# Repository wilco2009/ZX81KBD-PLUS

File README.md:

# ZX81KBD-PLUS
 Joystick, PS2 & USB keyboard interface for the ZX81

 ## INTERFACE COMPONENTS

 COMPONENT LIST
 |  Component |  Quantity |
 | ------| --------| 
 | Arduino nano R3	1
 | Push Button 6x6 | 2
 | DB9 male	| 1
 | Mini DIN	9 PIN | 1
 | PCF8574P	| 1
 | USB Host Shield	| 1
 | OLED 128x32 I2C	| 1
 | XC9572XL-PLCC44	| 1
 | LM1117 3v3 regulator SOT223| 1
 | Res 100K	| 2
 | Res 4K7	| 8
 | DIP16 socket	| 1
 | PLCC44 socket (Though hole)	| 1
 | pin header male 1x40 | 1
 | pin header male 1x40 (long pins)	| 1
 | pin header female 1x40	| 2
 | 74AHC125D SOP14	| 1
 | EDGE CONNECTOR | 1
 
Once the interface is assembled, the first thing we have to do is program the arduino (using the arduino IDE) or the avrdude.
We must also program the CPLD using the Xilinx IMPACT program and connecting a programming cable to the JTAG connector.

## REPLACING THE USB HOST SHIELD CHIP
Unless we buy an original USB Host Shield from the official Arduino store, it is very likely that we will end up with a defective board from Aliexpress. The Chinese manufacturers have not strictly followed the original scheme and have used a 74HC125D instead of a 74AHC125D indicated in the original scheme.

The good news is that by replacing this chip it is very likely that we will have a fully functional board, the bad news is that we will have to desolder the old chip and solder the new one.
In the photo you can see the chip that needs to be replaced.

## MAIN SCREEN

The main screen of the OLED display is divided into two sections.
On the left we have a representation of the zx81 keyboard, and on the right a representation of the joystick with its three buttons (A B and FIRE)
When you press any key on the keyboard or any button on the joystick we will see the pressure on the display.
Additionally, in the joystick section we can see which keys are configured for each of the joystick buttons.

## INTERFACE CONFIGURATION

To enter the configuration menu we can do it in two ways:
- Pressing the configuration button
- Pressing F10 on the keyboard

Once inside the menu we can move through the options using the joystick or the keyboard cursor arrows. 
To select an option we will press the fire button on the joystick or the enter key on the keyboard.

### SELECTION OF KEYBOARD LAYOUT

The first option that appears when we access the menu is the one that will allow us to choose the keyboard layout.

The system is prepared for the following distributions:
- "US" - USA
- "UK" - United Kingdom
- "ES" - Spain
- "DE" - Germany

The active keyboard will be marked with an asterisk.
We can change the active keyboard with the up/down arrows on the keyboard or joystick and select with enter or the fire button.
The ESC key will return to the main menu.

### REDEFINING JOYSTICK KEYS

To redefine the joystick keys we will select the second option from the main menu by moving down with the arrow and press enter/fire.
After this, a screen identical to the main screen will appear but with the first joystick button to be redefined (UP) flashing.
We will select the key we want with the arrows in the left section of the screen and press ENTER or fire.
We can also directly press the key that we want to assign, except in the case of the cursor and enter keys, which would have to be selected by the first method mentioned.
By pressing the ESC or A key on the joystick we will go to the next button without modifying the current one.

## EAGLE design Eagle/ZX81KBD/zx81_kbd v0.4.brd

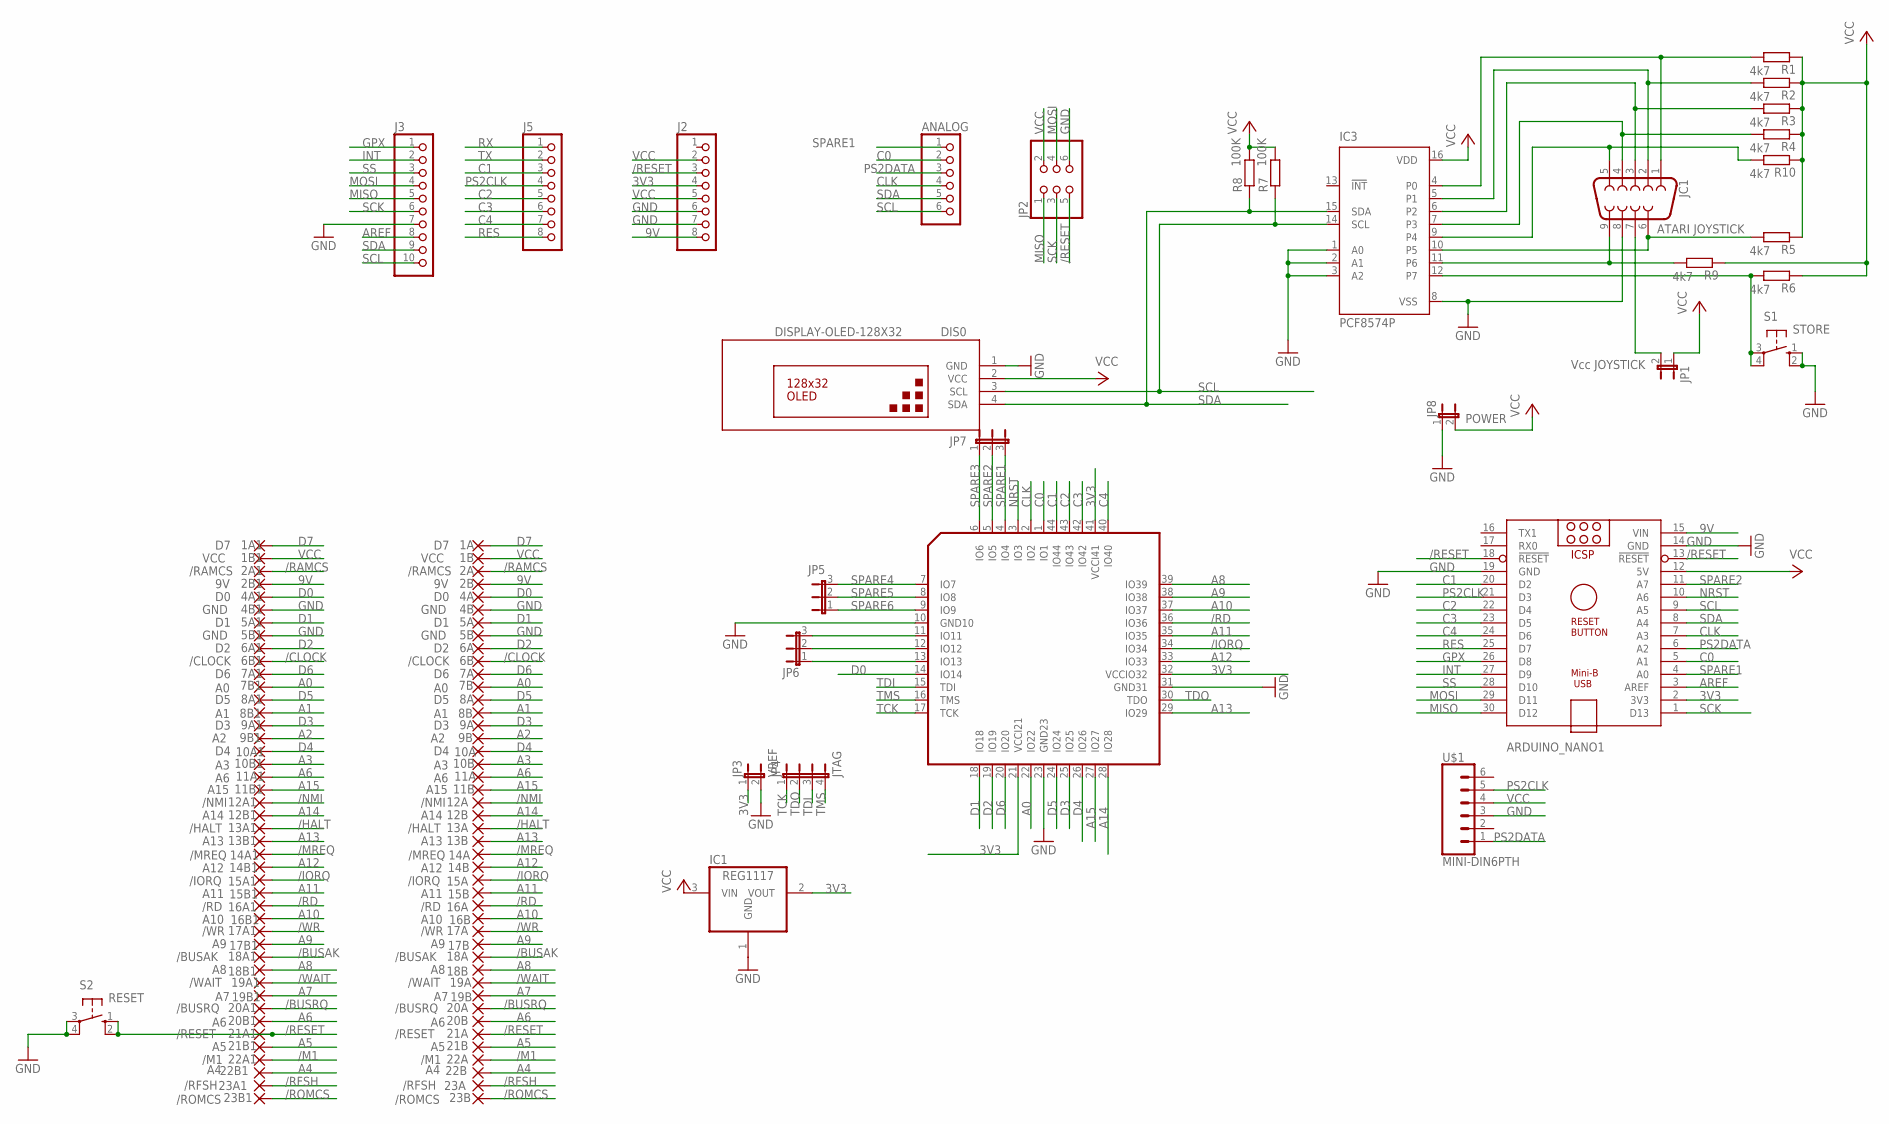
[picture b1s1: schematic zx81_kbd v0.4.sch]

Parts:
1A, 1A1: D7; EDGEPIN
1B, 1B1: VCC; EDGEPIN
2A, 2A1: /RAMCS; EDGEPIN
2B, 2B1: 9V; EDGEPIN
4A, 4A1: D0; EDGEPIN
4B, 4B1, 5B, 5B1: GND; EDGEPIN
5A, 5A1: D1; EDGEPIN
6A, 6A1: D2; EDGEPIN
6B, 6B1: /CLOCK; EDGEPIN
7A, 7A1: D6; EDGEPIN
7B, 7B1: A0; EDGEPIN
8A, 8A1: D5; EDGEPIN
8B, 8B1: A1; EDGEPIN
9A, 9A1: D3; EDGEPIN
9B, 9B1: A2; EDGEPIN
10A, 10A1: D4; EDGEPIN
10B, 10B1: A3; EDGEPIN
11A, 11A1, 20B, 20B1: A6; EDGEPIN
11B, 11B1: A15; EDGEPIN
12A, 12A1: /NMI; EDGEPIN
12B, 12B1: A14; EDGEPIN
13A, 13A1: /HALT; EDGEPIN
13B, 13B1: A13; EDGEPIN
14A, 14A1: /MREQ; EDGEPIN
14B, 14B1: A12; EDGEPIN
15A, 15A1: /IORQ; EDGEPIN
15B, 15B1: A11; EDGEPIN
16A, 16A1: /RD; EDGEPIN
16B, 16B1: A10; EDGEPIN
17A, 17A1: /WR; EDGEPIN
17B, 17B1: A9; EDGEPIN
18A, 18A1: /BUSAK; EDGEPIN
18B, 18B1: A8; EDGEPIN
19A, 19A1: /WAIT; EDGEPIN
19B, 19B1: A7; EDGEPIN
20A, 20A1: /BUSRQ; EDGEPIN
21A, 21A1: /RESET; EDGEPIN
21B, 21B1: A5; EDGEPIN
22A, 22A1: /M1; EDGEPIN
22B, 22B1: A4; EDGEPIN
23A, 23A1: /RFSH; EDGEPIN
23B, 23B1: /ROMCS; EDGEPIN
ANALOG: PINHD-1X6; 1X06
ARDUINO_NANO1: ARDUINO_NANO
DIS0: DISPLAY-OLED-128X32
IC1: REG1117; SOT223
IC3: PCF8574P; DIL16
J2, J5: PINHD-1X8; 1X08
J3: PINHD-1X10; 1X10
JC1: ATARI JOYSTICK; DB9_MALE
JP1: Vcc JOYSTICK; JP1
JP2: PINHD-2X3; 2X03
JP3: VREF; JP1
JP4: JTAG; JP4
JP5, JP6, JP7: JP2E; JP2
JP8: POWER; JP1
R1, R2, R3, R4, R5, R6, R9, R10: 4k7; 0204/7
R7, R8: 100K; 0204/7
S1: STORE; B3F-10XX_11MM
S2: RESET; B3F-10XX_11MM
U$1: MINI-DIN6PTH; MINI-DIN6
XC95CPLD: XC9572PLC; 3M44

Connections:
3V3: ARDUINO_NANO1.2 (3V3), IC1.2 (VOUT), J2.4, JP3.1, XC95CPLD.21 (VCCI21), XC95CPLD.32 (VCCIO32), XC95CPLD.41 (VCCI41)
9V: 2B.1, 2B1.1, ARDUINO_NANO1.15 (VIN), J2.8
/BUSAK: 18A.1, 18A1.1
/BUSRQ: 20A.1, 20A1.1
/CLOCK: 6B.1, 6B1.1
/HALT: 13A.1, 13A1.1
/IORQ: 15A.1, 15A1.1, XC95CPLD.34 (IO34)
/M1: 22A.1, 22A1.1
/MREQ: 14A.1, 14A1.1
/NMI: 12A.1, 12A1.1
/RAMCS: 2A.1, 2A1.1
/RD: 16A.1, 16A1.1, XC95CPLD.36 (IO36)
/RESET: 21A.1, 21A1.1, ARDUINO_NANO1.13 (!RESET), ARDUINO_NANO1.18 (!RESET), J2.3, JP2.5, S2.1 (S), S2.2 (S1)
/RFSH: 23A.1, 23A1.1
/ROMCS: 23B.1, 23B1.1
/WAIT: 19A.1, 19A1.1
/WR: 17A.1, 17A1.1
A0: 7B.1, 7B1.1, XC95CPLD.22 (IO22)
A1: 8B.1, 8B1.1
A2: 9B.1, 9B1.1
A3: 10B.1, 10B1.1
A4: 22B.1, 22B1.1
A5: 21B.1, 21B1.1
A6: 11A.1, 11A1.1, 20B.1, 20B1.1
A7: 19B.1, 19B1.1
A8: 18B.1, 18B1.1, XC95CPLD.39 (IO39)
A9: 17B.1, 17B1.1, XC95CPLD.38 (IO38)
A10: 16B.1, 16B1.1, XC95CPLD.37 (IO37)
A11: 15B.1, 15B1.1, XC95CPLD.35 (IO35)
A12: 14B.1, 14B1.1, XC95CPLD.33 (IO33)
A13: 13B.1, 13B1.1, XC95CPLD.29 (IO29)
A14: 12B.1, 12B1.1, XC95CPLD.28 (IO28)
A15: 11B.1, 11B1.1, XC95CPLD.27 (IO27)
AREF: ARDUINO_NANO1.3 (AREF), J3.8
C0: ANALOG.2, ARDUINO_NANO1.5 (A1), XC95CPLD.1 (IO1)
C1: ARDUINO_NANO1.20 (D2), J5.3, XC95CPLD.44 (IO44)
C2: ARDUINO_NANO1.22 (D4), J5.5, XC95CPLD.43 (IO43)
C3: ARDUINO_NANO1.23 (D5), J5.6, XC95CPLD.42 (IO42)
C4: ARDUINO_NANO1.24 (D6), J5.7, XC95CPLD.40 (IO40)
CLK: ANALOG.4, ARDUINO_NANO1.7 (A3), XC95CPLD.2 (IO2)
D0: 4A.1, 4A1.1, XC95CPLD.14 (IO14)
D1: 5A.1, 5A1.1, XC95CPLD.18 (IO18)
D2: 6A.1, 6A1.1, XC95CPLD.19 (IO19)
D3: 9A.1, 9A1.1, XC95CPLD.25 (IO25)
D4: 10A.1, 10A1.1, XC95CPLD.26 (IO26)
D5: 8A.1, 8A1.1, XC95CPLD.24 (IO24)
D6: 7A.1, 7A1.1, XC95CPLD.20 (IO20)
D7: 1A.1, 1A1.1
GND: 4B.1, 4B1.1, 5B.1, 5B1.1, ARDUINO_NANO1.14 (GND), ARDUINO_NANO1.19 (GND), DIS0.1 (GND), IC1.1 (GND), IC3.1 (A0), IC3.2 (A1), IC3.3 (A2), IC3.8 (VSS), J2.6, J2.7, J3.7, JC1.8, JP2.6, JP3.2, JP8.1, S1.1 (S), S1.2 (S1), S2.3, S2.4 (P1), U$1.3, XC95CPLD.10 (GND10), XC95CPLD.23 (GND23), XC95CPLD.31 (GND31)
GPX: ARDUINO_NANO1.26 (D8), J3.1
INT: ARDUINO_NANO1.27 (D9), J3.2
MISO: ARDUINO_NANO1.30 (D12), J3.5, JP2.1
MOSI: ARDUINO_NANO1.29 (D11), J3.4, JP2.4
unnamed: JP6.3, XC95CPLD.11 (IO11)
unnamed: JP6.2, XC95CPLD.12 (IO12)
unnamed: JP6.1, XC95CPLD.13 (IO13)
unnamed: IC3.4 (P0), JC1.1, R1.2
unnamed: IC3.5 (P1), JC1.2, R2.2
unnamed: IC3.6 (P2), JC1.3, R3.2
unnamed: IC3.7 (P3), JC1.4, R4.2
unnamed: IC3.10 (P5), JC1.6, R5.2
unnamed: IC3.9 (P4), JC1.5, R10.2
unnamed: IC3.12 (P7), R6.2, S1.3, S1.4 (P1)
unnamed: JC1.7, JP1.2
unnamed: IC3.11 (P6), JC1.9, R9.2
NRST: ARDUINO_NANO1.10 (A6), XC95CPLD.3 (IO3)
PS2CLK: ARDUINO_NANO1.21 (D3), J5.4, U$1.5
PS2DATA: ANALOG.3, ARDUINO_NANO1.6 (A2), U$1.1
RES: ARDUINO_NANO1.25 (D7), J5.8
RX: J5.1
SCK: ARDUINO_NANO1.1 (D13), J3.6, JP2.3
SCL: ANALOG.6, ARDUINO_NANO1.9 (A5), DIS0.3 (SCL), IC3.14 (SCL), J3.10, R7.1
SDA: ANALOG.5, ARDUINO_NANO1.8 (A4), DIS0.4 (SDA), IC3.15 (SDA), J3.9, R8.1
SPARE1: ANALOG.1, ARDUINO_NANO1.4 (A0), JP7.3, XC95CPLD.4 (IO4)
SPARE2: ARDUINO_NANO1.11 (A7), JP7.2, XC95CPLD.5 (IO5)
SPARE3: JP7.1, XC95CPLD.6 (IO6)
SPARE4: JP5.3, XC95CPLD.7 (IO7)
SPARE5: JP5.2, XC95CPLD.8 (IO8)
SPARE6: JP5.1, XC95CPLD.9 (IO9)
SS: ARDUINO_NANO1.28 (D10), J3.3
TCK: JP4.1, XC95CPLD.17 (TCK)
TDI: JP4.3, XC95CPLD.15 (TDI)
TDO: JP4.2, XC95CPLD.30 (TDO)
TMS: JP4.4, XC95CPLD.16 (TMS)
TX: J5.2
VCC: 1B.1, 1B1.1, ARDUINO_NANO1.12 (5V), DIS0.2 (VCC), IC1.3 (VIN), IC3.16 (VDD), J2.2, J2.5, JP1.1, JP2.2, JP8.2, R1.1, R2.1, R3.1, R4.1, R5.1, R6.1, R7.2, R8.2, R9.1, R10.1, U$1.4

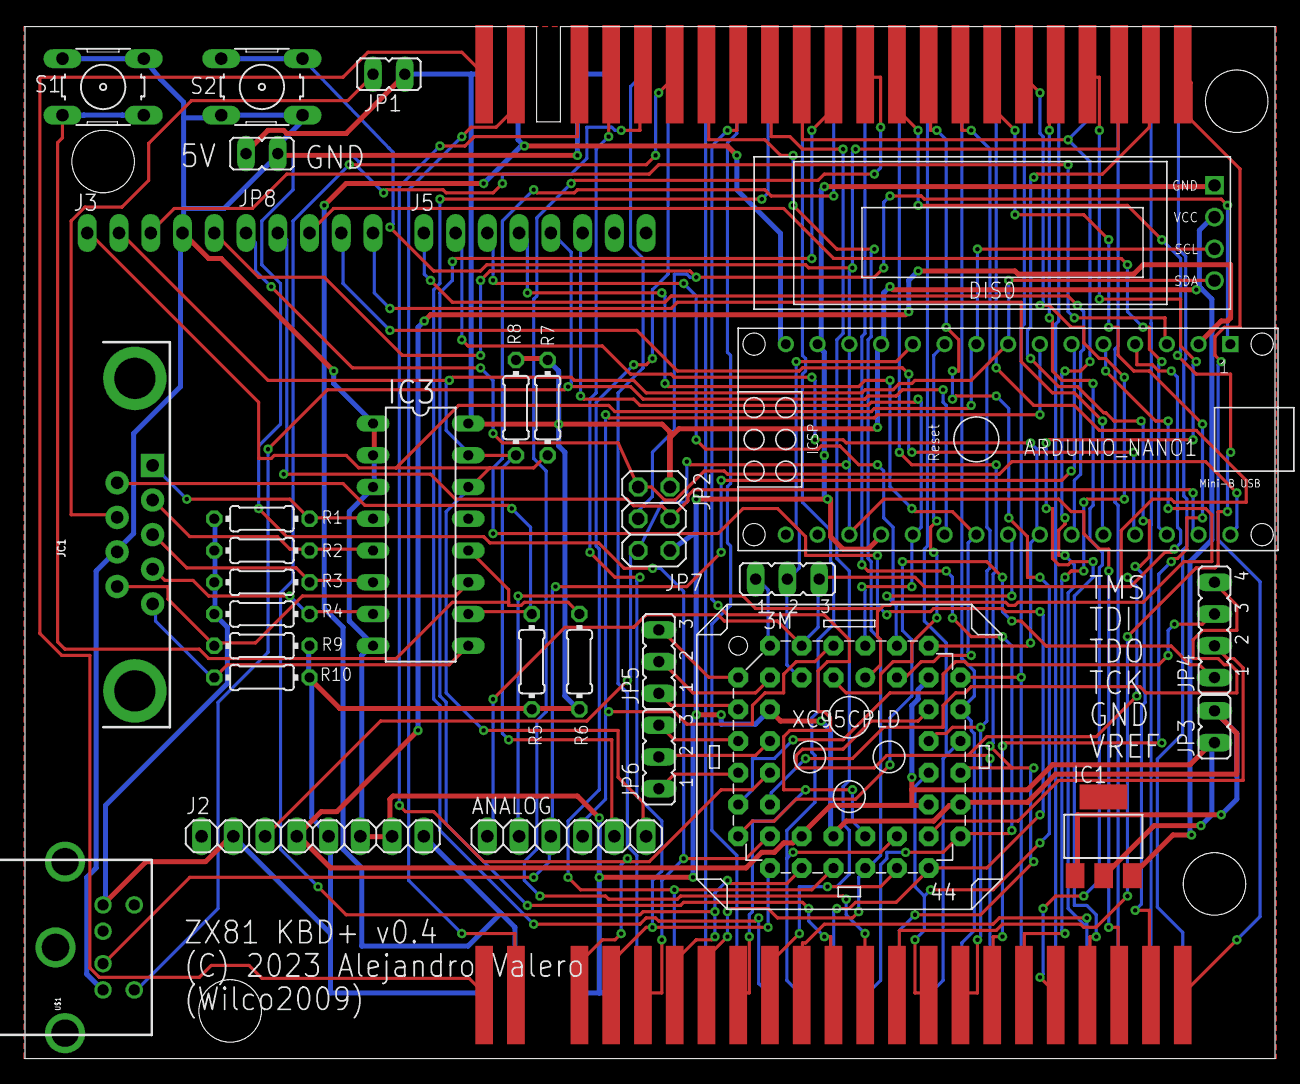
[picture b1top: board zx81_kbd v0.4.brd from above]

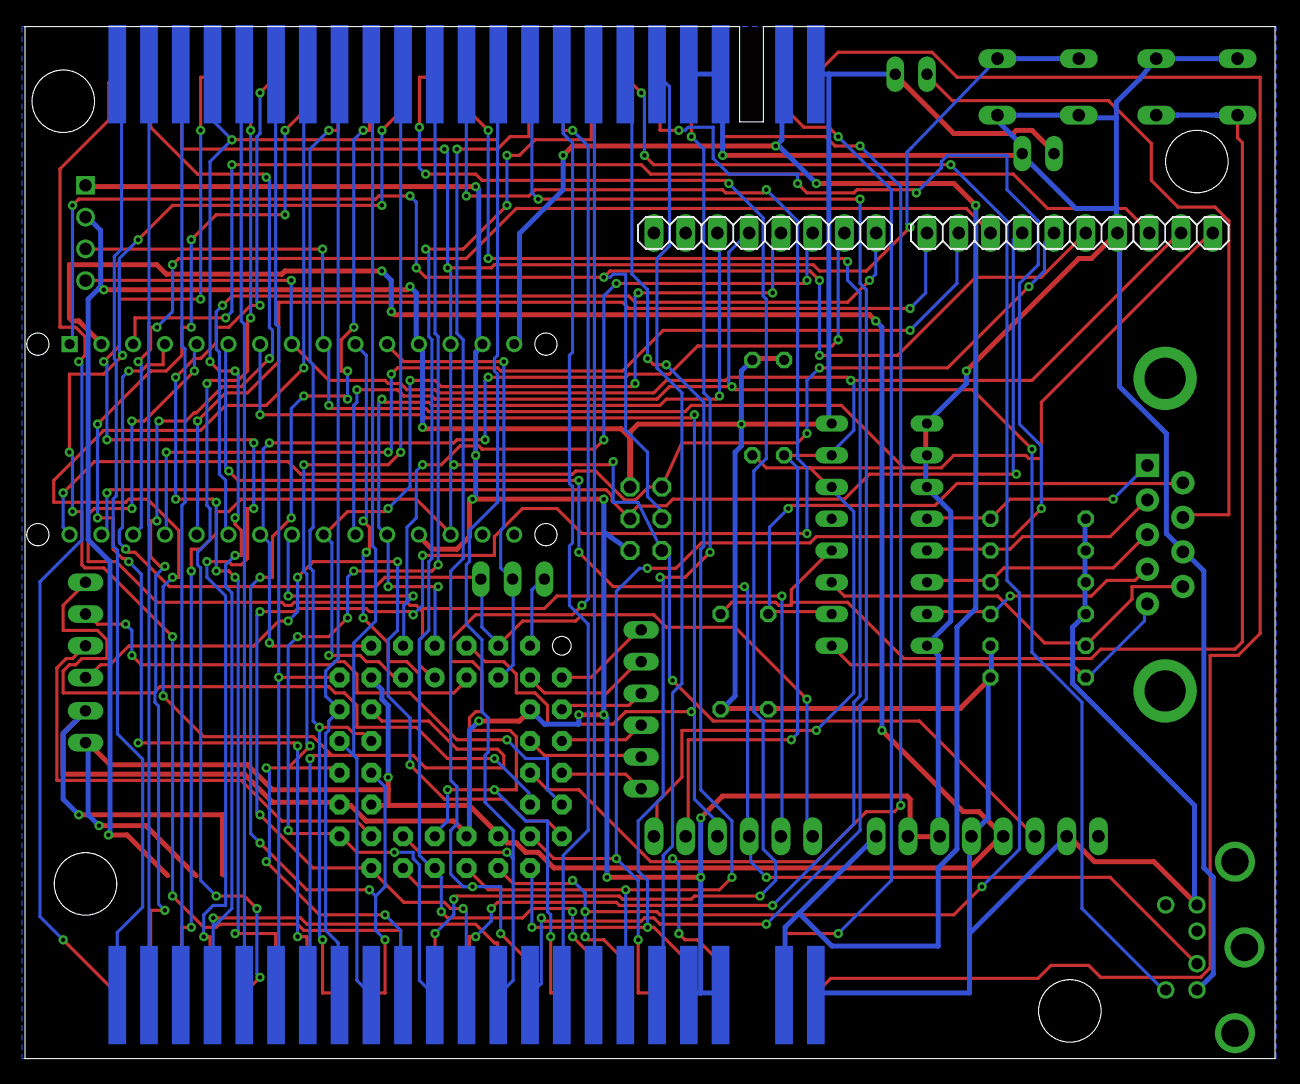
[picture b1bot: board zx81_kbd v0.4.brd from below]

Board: 2 copper layers, 100.0 x 82.5 mm, 119 parts (46 on the bottom side), 84 nets.

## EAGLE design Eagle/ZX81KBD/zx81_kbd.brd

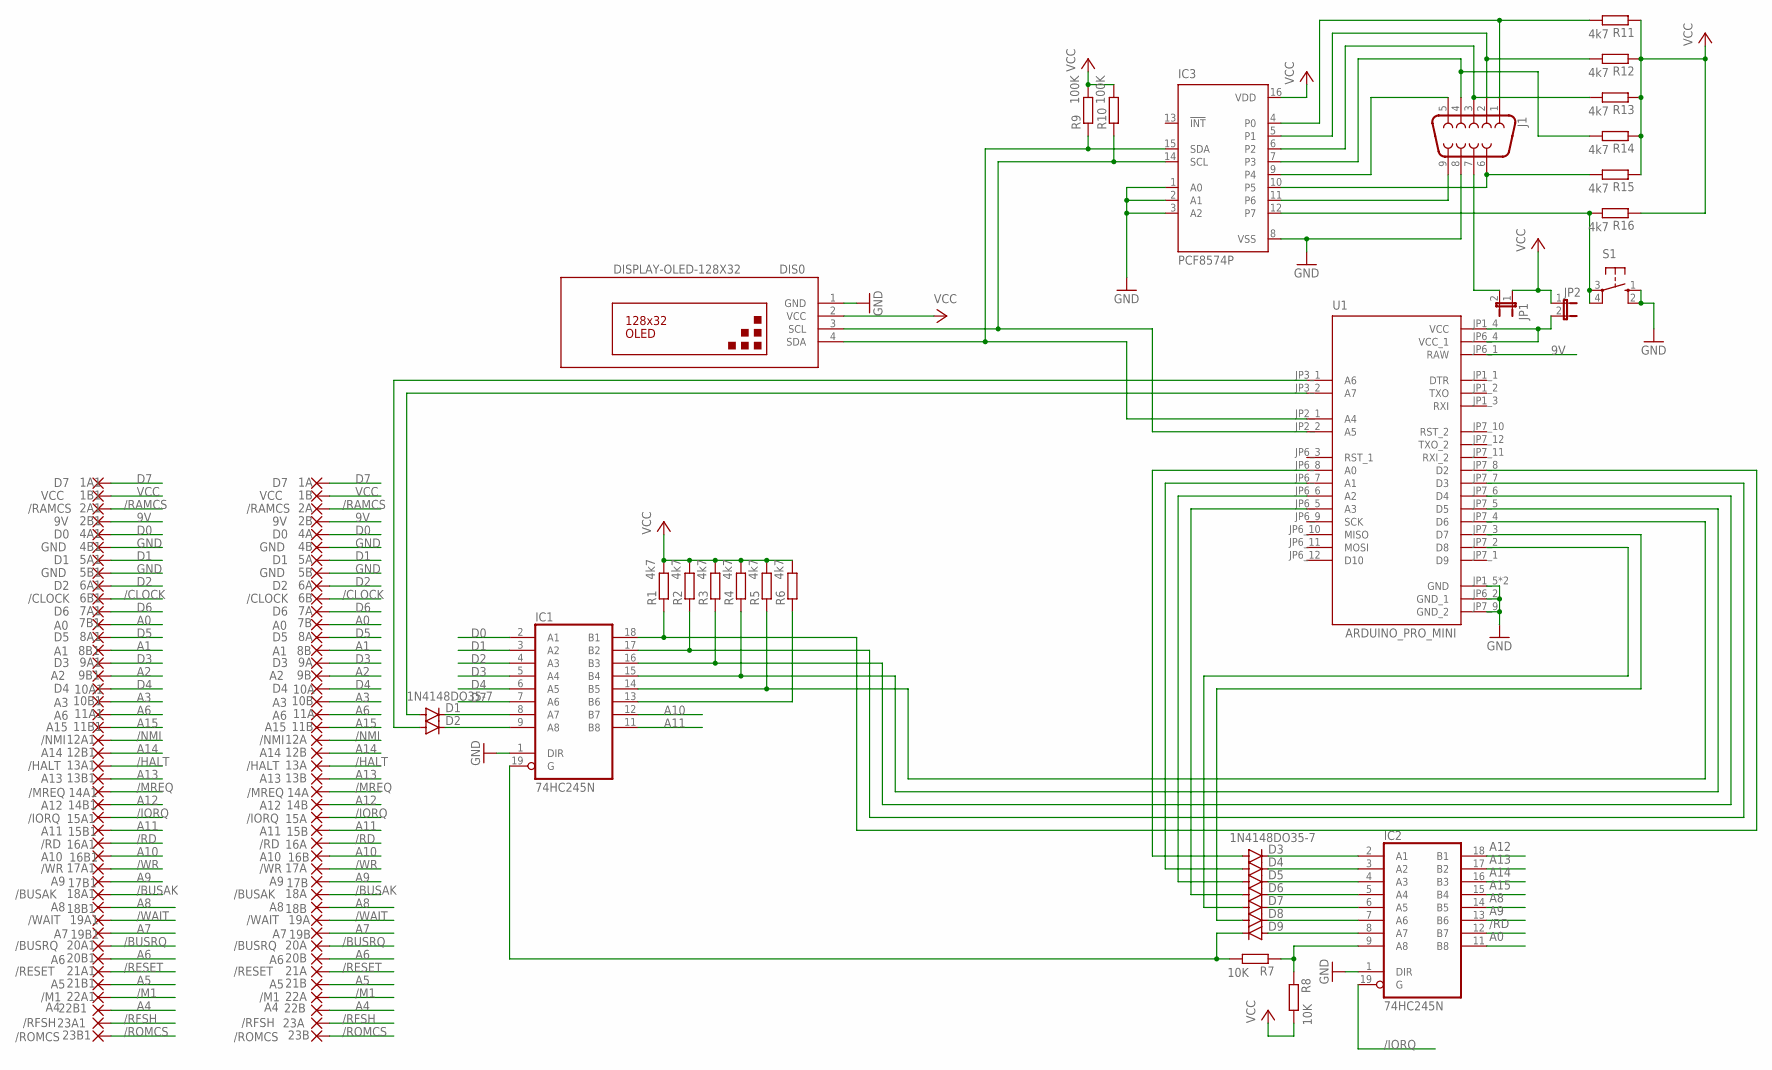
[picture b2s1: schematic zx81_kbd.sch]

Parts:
1A, 1A1: D7; EDGEPIN
1B, 1B1: VCC; EDGEPIN
2A, 2A1: /RAMCS; EDGEPIN
2B, 2B1: 9V; EDGEPIN
4A, 4A1: D0; EDGEPIN
4B, 4B1, 5B, 5B1: GND; EDGEPIN
5A, 5A1: D1; EDGEPIN
6A, 6A1: D2; EDGEPIN
6B, 6B1: /CLOCK; EDGEPIN
7A, 7A1: D6; EDGEPIN
7B, 7B1: A0; EDGEPIN
8A, 8A1: D5; EDGEPIN
8B, 8B1: A1; EDGEPIN
9A, 9A1: D3; EDGEPIN
9B, 9B1: A2; EDGEPIN
10A, 10A1: D4; EDGEPIN
10B, 10B1: A3; EDGEPIN
11A, 11A1, 20B, 20B1: A6; EDGEPIN
11B, 11B1: A15; EDGEPIN
12A, 12A1: /NMI; EDGEPIN
12B, 12B1: A14; EDGEPIN
13A, 13A1: /HALT; EDGEPIN
13B, 13B1: A13; EDGEPIN
14A, 14A1: /MREQ; EDGEPIN
14B, 14B1: A12; EDGEPIN
15A, 15A1: /IORQ; EDGEPIN
15B, 15B1: A11; EDGEPIN
16A, 16A1: /RD; EDGEPIN
16B, 16B1: A10; EDGEPIN
17A, 17A1: /WR; EDGEPIN
17B, 17B1: A9; EDGEPIN
18A, 18A1: /BUSAK; EDGEPIN
18B, 18B1: A8; EDGEPIN
19A, 19A1: /WAIT; EDGEPIN
19B, 19B1: A7; EDGEPIN
20A, 20A1: /BUSRQ; EDGEPIN
21A, 21A1: /RESET; EDGEPIN
21B, 21B1: A5; EDGEPIN
22A, 22A1: /M1; EDGEPIN
22B, 22B1: A4; EDGEPIN
23A, 23A1: /RFSH; EDGEPIN
23B, 23B1: /ROMCS; EDGEPIN
D1, D2, D3, D4, D5, D6, D7, D8, D9: 1N4148DO35-7; DO35-7
DIS0: DISPLAY-OLED-128X32
IC1, IC2: 74HC245N; DIL20
IC3: PCF8574P; DIL16
J1: DB9MALE; DB9_MALE
JP1, JP2: JP1E; JP1
R1, R2, R3, R4, R5, R6, R11, R12, R13, R14, R15, R16: 4k7; 0204/7
R7, R8: 10K; 0204/7
R9, R10: 100K; 0204/7
S1: 10-XX11MM; B3F-10XX_11MM
U1: ARDUINO_PRO_MINI; MODULE_ARDUINO_PRO_MINI

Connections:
9V: 2B.1, 2B1.1, U1.JP6_1 (RAW)
/BUSAK: 18A.1, 18A1.1
/BUSRQ: 20A.1, 20A1.1
/CLOCK: 6B.1, 6B1.1
/HALT: 13A.1, 13A1.1
/IORQ: 15A.1, 15A1.1, IC2.19 (G)
/M1: 22A.1, 22A1.1
/MREQ: 14A.1, 14A1.1
/NMI: 12A.1, 12A1.1
/RAMCS: 2A.1, 2A1.1
/RD: 16A.1, 16A1.1, IC2.12 (B7)
/RESET: 21A.1, 21A1.1
/RFSH: 23A.1, 23A1.1
/ROMCS: 23B.1, 23B1.1
/WAIT: 19A.1, 19A1.1
/WR: 17A.1, 17A1.1
A0: 7B.1, 7B1.1, IC2.11 (B8)
A1: 8B.1, 8B1.1
A2: 9B.1, 9B1.1
A3: 10B.1, 10B1.1
A4: 22B.1, 22B1.1
A5: 21B.1, 21B1.1
A6: 11A.1, 11A1.1, 20B.1, 20B1.1
A7: 19B.1, 19B1.1
A8: 18B.1, 18B1.1, IC2.14 (B5)
A9: 17B.1, 17B1.1, IC2.13 (B6)
A10: 16B.1, 16B1.1, IC1.12 (B7)
A11: 15B.1, 15B1.1, IC1.11 (B8)
A12: 14B.1, 14B1.1, IC2.18 (B1)
A13: 13B.1, 13B1.1, IC2.17 (B2)
A14: 12B.1, 12B1.1, IC2.16 (B3)
A15: 11B.1, 11B1.1, IC2.15 (B4)
D0: 4A.1, 4A1.1, IC1.2 (A1)
D1: 5A.1, 5A1.1, IC1.3 (A2)
D2: 6A.1, 6A1.1, IC1.4 (A3)
D3: 9A.1, 9A1.1, IC1.5 (A4)
D4: 10A.1, 10A1.1, IC1.6 (A5)
D5: 8A.1, 8A1.1
D6: 7A.1, 7A1.1
D7: 1A.1, 1A1.1, IC1.7 (A6)
GND: 4B.1, 4B1.1, 5B.1, 5B1.1, DIS0.1 (GND), IC1.1 (DIR), IC1.10 (GND), IC2.1 (DIR), IC2.10 (GND), IC3.1 (A0), IC3.2 (A1), IC3.3 (A2), IC3.8 (VSS), J1.8, S1.1 (S), S1.2 (S1), U1.JP1_5 (GND), U1.JP1_6 (GND), U1.JP6_2 (GND_1), U1.JP7_9 (GND_2)
unnamed: D3.C, IC2.2 (A1)
unnamed: IC1.18 (B1), R1.1, U1.JP7_8 (D2)
unnamed: IC1.17 (B2), R2.1, U1.JP7_7 (D3)
unnamed: IC1.16 (B3), R3.1, U1.JP7_6 (D4)
unnamed: JP2.2, U1.JP1_4 (VCC), U1.JP6_4 (VCC_1)
unnamed: IC1.14 (B5), R5.1, U1.JP7_4 (D6)
unnamed: IC1.13 (B6), R6.1
unnamed: D4.C, IC2.3 (A2)
unnamed: D5.C, IC2.4 (A3)
unnamed: D6.C, IC2.5 (A4)
unnamed: D7.C, IC2.6 (A5)
unnamed: D8.C, IC2.7 (A6)
unnamed: D9.A, IC2.8 (A7)
unnamed: IC2.9 (A8), R7.1, R8.1
unnamed: D1.A, U1.JP3_2 (A7)
unnamed: D1.C, IC1.8 (A7)
unnamed: D2.C, IC1.9 (A8)
unnamed: D9.C, IC1.19 (G), R7.2
unnamed: D2.A, U1.JP3_1 (A6)
unnamed: DIS0.4 (SDA), IC3.15 (SDA), R9.1, U1.JP2_1 (A4)
unnamed: DIS0.3 (SCL), IC3.14 (SCL), R10.1, U1.JP2_2 (A5)
unnamed: D6.A, U1.JP6_5 (A3)
unnamed: D5.A, U1.JP6_6 (A2)
unnamed: D4.A, U1.JP6_7 (A1)
unnamed: D7.A, U1.JP7_2 (D8)
unnamed: D8.A, U1.JP7_3 (D7)
unnamed: IC3.4 (P0), J1.1, R11.2
unnamed: IC1.15 (B4), R4.1, U1.JP7_5 (D5)
unnamed: D3.A, U1.JP6_8 (A0)
unnamed: IC3.5 (P1), J1.2, R12.2
unnamed: IC3.6 (P2), J1.3, R13.2
unnamed: IC3.7 (P3), J1.4, R14.2
unnamed: IC3.10 (P5), J1.6, R15.2
unnamed: IC3.9 (P4), J1.5
unnamed: IC3.12 (P7), R16.2, S1.3, S1.4 (P1)
unnamed: J1.7, JP1.2
unnamed: IC3.11 (P6), J1.9
VCC: 1B.1, 1B1.1, DIS0.2 (VCC), IC1.20 (VCC), IC2.20 (VCC), IC3.16 (VDD), JP1.1, JP2.1, R1.2, R2.2, R3.2, R4.2, R5.2, R6.2, R8.2, R9.2, R10.2, R11.1, R12.1, R13.1, R14.1, R15.1, R16.1

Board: 2 copper layers, 122 parts (44 on the bottom side), 79 nets, no tracks yet.

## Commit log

2023-11-19 Initial
2023-12-02 USB Keyboard
2023-12-02 USB Keyboard working
2023-12-03 pruebas
2023-12-11 Initial public version
2023-12-11 initial public versioninitial public version

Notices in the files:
Eagle/ZX81KBD/zx81_kbd v0.4.brd:
(C) 2023 Alejandro Valero
parts and their libraries:
SparkFun-Connectors: Licensing: Creative Commons ShareAlike 4.0 International - https://creativecommons.org/licenses/by-sa/4.0
diy-modules: Released under the Creative Commons Attribution 4.0 International License: http://creativecommons.org/licenses/by/4.0
